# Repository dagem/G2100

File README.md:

# G2100
  a Cherry G80-2100 with modern features

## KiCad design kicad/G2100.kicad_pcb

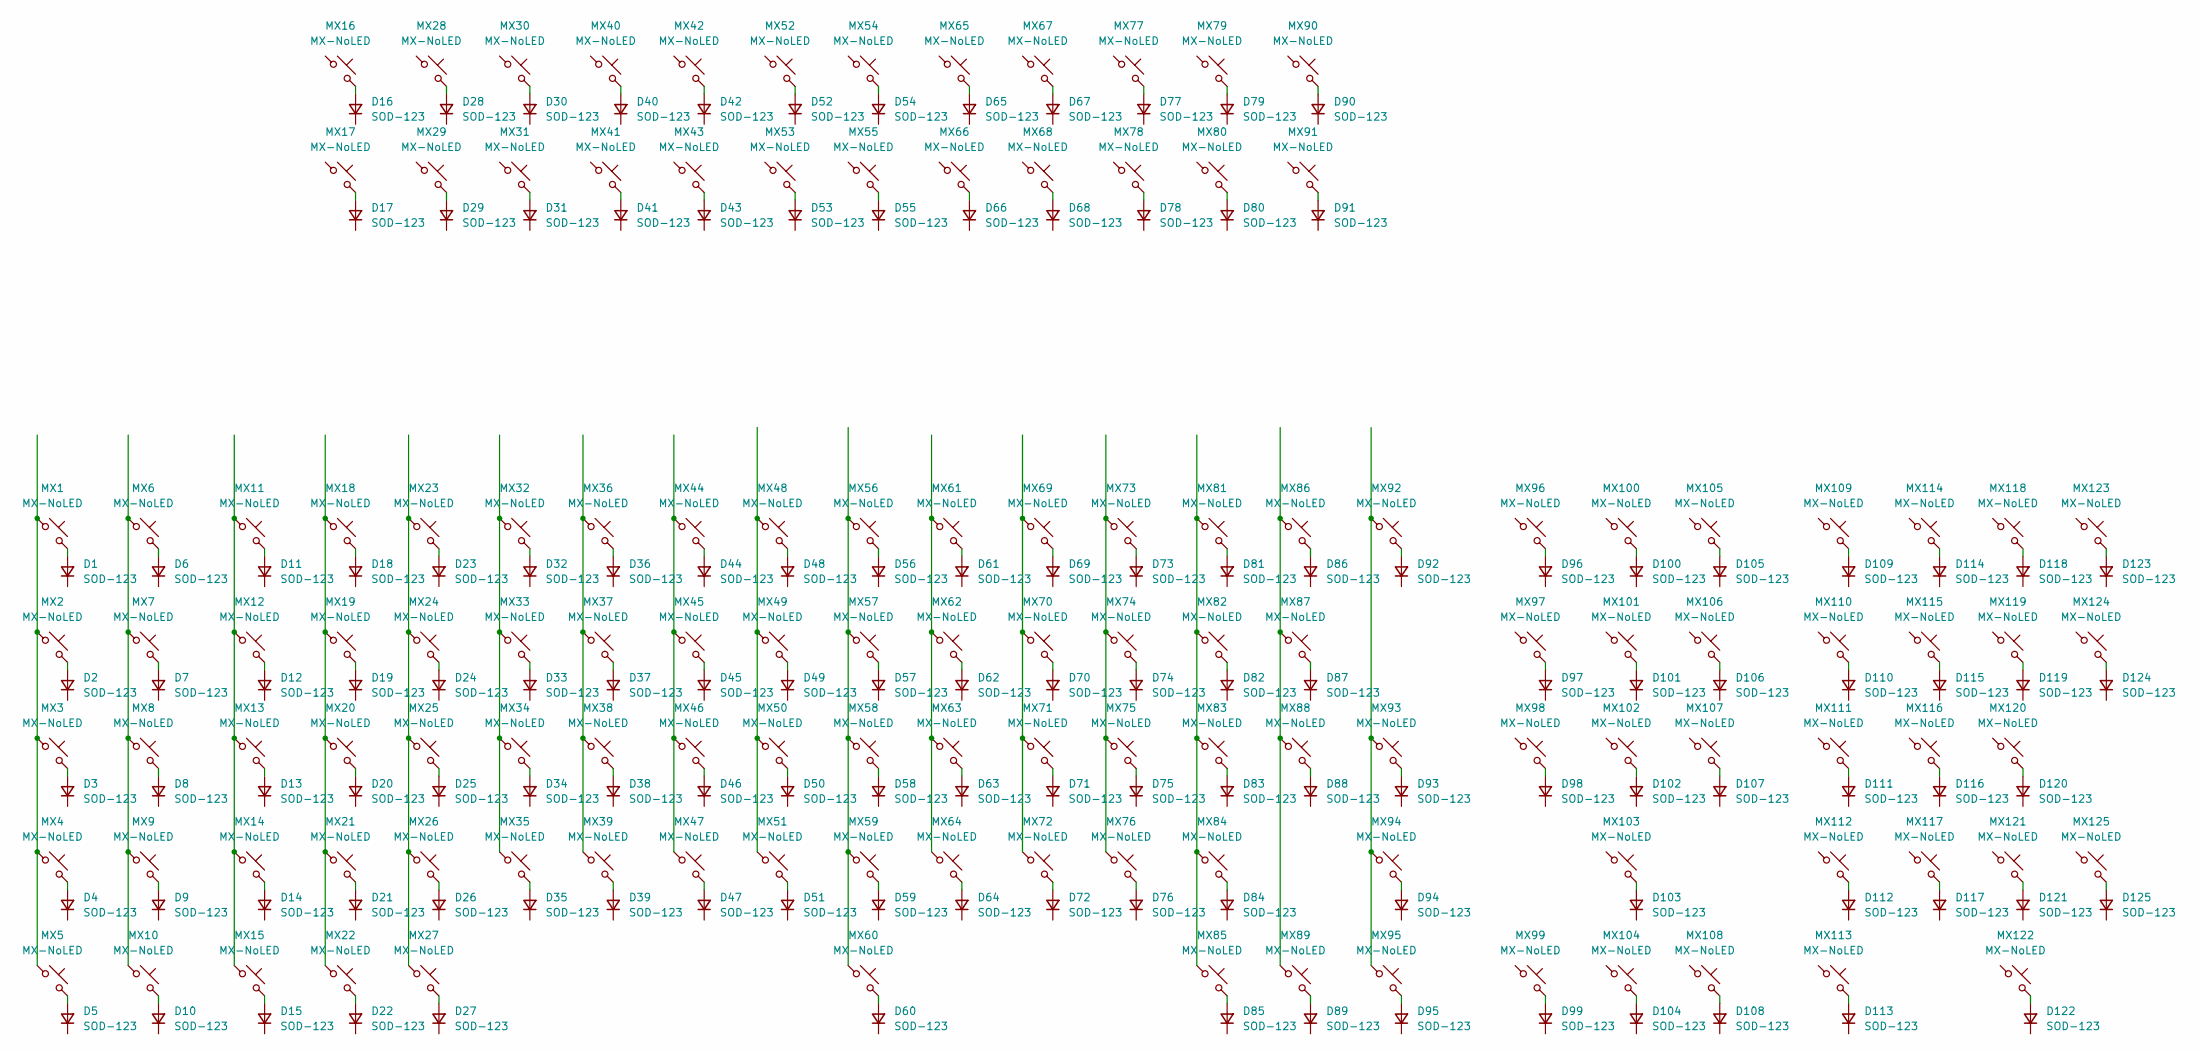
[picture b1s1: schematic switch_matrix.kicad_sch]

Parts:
D1, D2, D3, D4, D5, D6, D7, D8, D9, D10, D11, D12, D13, D14, D15, D16, D17, D18, D19, D20, D21, D22, D23, D24, D25, D26, D27, D28, D29, D30, D31, D32, D33, D34, D35, D36, D37, D38, D39, D40, D41, D42, D43, D44, D45, D46, D47, D48, D49, D50, D51, D52, D53, D54, D55, D56, D57, D58, D59, D60, D61, D62, D63, D64, D65, D66, D67, D68, D69, D70, D71, D72, D73, D74, D75, D76, D77, D78, D79, D80, D81, D82, D83, D84, D85, D86, D87, D88, D89, D90, D91, D92, D93, D94, D95, D96, D97, D98, D99, D100, D101, D102, D103, D104, D105, D106, D107, D108, D109, D110, D111, D112, D113, D114, D115, D116, D117, D118, D119, D120, D121, D122, D123, D124, D125: SOD-123; D_SOD-123
MX1, MX2, MX3, MX4, MX5, MX6, MX7, MX8, MX9, MX10, MX11, MX16, MX17, MX18, MX19, MX20, MX21, MX22, MX23, MX24, MX25, MX26, MX28, MX29, MX30, MX31, MX32, MX33, MX34, MX35, MX36, MX37, MX38, MX39, MX40, MX41, MX42, MX43, MX44, MX45, MX46, MX47, MX48, MX49, MX50, MX51, MX52, MX53, MX54, MX55, MX56, MX57, MX58, MX59, MX61, MX62, MX63, MX64, MX65, MX66, MX67, MX68, MX69, MX70, MX71, MX72, MX73, MX74, MX75, MX76, MX77, MX78, MX79, MX80, MX81, MX82, MX83, MX84, MX86, MX87, MX88, MX89, MX90, MX91, MX96, MX97, MX98, MX99, MX100, MX101, MX102, MX103, MX104, MX105, MX106, MX107, MX108, MX109, MX110, MX111, MX112, MX114, MX115, MX116, MX117, MX118, MX119, MX120, MX121, MX122, MX123: MX-NoLED; MX-Hotswap-1U
MX12, MX15, MX27, MX85, MX95: MX-NoLED; MX-Hotswap-1.5U
MX13: MX-NoLED; MX-Hotswap-1.75U
MX14: MX-NoLED; MX-Hotswap-1.25U
MX60: MX-NoLED; MX-Hotswap-7U
MX92, MX113: MX-NoLED; MX-Hotswap-2U
MX93: MX-NoLED; MX-Hotswap-ISO-Rotated
MX94: MX-NoLED; MX-Hotswap-2.75U
MX124, MX125: MX-NoLED; MX-Hotswap-2U-Vertical

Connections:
unnamed: D1.2 (A_2), MX1.2
unnamed: D2.2 (A_2), MX2.2
unnamed: D3.2 (A_2), MX3.2
unnamed: D4.2 (A_2), MX4.2
unnamed: D5.2 (A_2), MX5.2
unnamed: D6.2 (A_2), MX6.2
unnamed: D7.2 (A_2), MX7.2
unnamed: D8.2 (A_2), MX8.2
unnamed: D9.2 (A_2), MX9.2
unnamed: D10.2 (A_2), MX10.2
unnamed: D11.2 (A_2), MX11.2
unnamed: D12.2 (A_2), MX12.2
unnamed: D13.2 (A_2), MX13.2
unnamed: D14.2 (A_2), MX14.2
unnamed: D15.2 (A_2), MX15.2
unnamed: D16.2 (A_2), MX16.2 (2_2)
unnamed: D17.2 (A_2), MX17.2 (2_2)
unnamed: D18.2 (A_2), MX18.2
unnamed: D19.2 (A_2), MX19.2
unnamed: D20.2 (A_2), MX20.2
unnamed: D21.2 (A_2), MX21.2
unnamed: D22.2 (A_2), MX22.2
unnamed: D23.2 (A_2), MX23.2
unnamed: D24.2 (A_2), MX24.2
unnamed: D25.2 (A_2), MX25.2
unnamed: D26.2 (A_2), MX26.2
unnamed: D27.2 (A_2), MX27.2
unnamed: D28.2 (A_2), MX28.2 (2_2)
unnamed: D29.2 (A_2), MX29.2 (2_2)
unnamed: D30.2 (A_2), MX30.2 (2_2)
unnamed: D31.2 (A_2), MX31.2 (2_2)
unnamed: D32.2 (A_2), MX32.2
unnamed: D33.2 (A_2), MX33.2
unnamed: D34.2 (A_2), MX34.2
unnamed: D35.2 (A_2), MX35.2
unnamed: D36.2 (A_2), MX36.2
unnamed: D37.2 (A_2), MX37.2
unnamed: D38.2 (A_2), MX38.2
unnamed: D39.2 (A_2), MX39.2
unnamed: D40.2 (A_2), MX40.2 (2_2)
unnamed: D41.2 (A_2), MX41.2 (2_2)
unnamed: D42.2 (A_2), MX42.2 (2_2)
unnamed: D43.2 (A_2), MX43.2 (2_2)
unnamed: D44.2 (A_2), MX44.2
unnamed: D45.2 (A_2), MX45.2
unnamed: D46.2 (A_2), MX46.2
unnamed: D47.2 (A_2), MX47.2
unnamed: D48.2 (A_2), MX48.2
unnamed: D49.2 (A_2), MX49.2
unnamed: D50.2 (A_2), MX50.2
unnamed: D51.2 (A_2), MX51.2
unnamed: D52.2 (A_2), MX52.2 (2_2)
unnamed: D53.2 (A_2), MX53.2 (2_2)
unnamed: D54.2 (A_2), MX54.2 (2_2)
unnamed: D55.2 (A_2), MX55.2 (2_2)
unnamed: D56.2 (A_2), MX56.2
unnamed: D57.2 (A_2), MX57.2
unnamed: D58.2 (A_2), MX58.2
unnamed: D59.2 (A_2), MX59.2
unnamed: D60.2 (A_2), MX60.2
unnamed: D61.2 (A_2), MX61.2
unnamed: D62.2 (A_2), MX62.2
unnamed: D63.2 (A_2), MX63.2
unnamed: D64.2 (A_2), MX64.2
unnamed: D65.2 (A_2), MX65.2 (2_2)
unnamed: D66.2 (A_2), MX66.2 (2_2)
unnamed: D67.2 (A_2), MX67.2 (2_2)
unnamed: D68.2 (A_2), MX68.2 (2_2)
unnamed: D69.2 (A_2), MX69.2
unnamed: D70.2 (A_2), MX70.2
unnamed: D71.2 (A_2), MX71.2
unnamed: D72.2 (A_2), MX72.2
unnamed: D73.2 (A_2), MX73.2
unnamed: D74.2 (A_2), MX74.2
unnamed: D75.2 (A_2), MX75.2
unnamed: D76.2 (A_2), MX76.2
unnamed: D77.2 (A_2), MX77.2 (2_2)
unnamed: D78.2 (A_2), MX78.2 (2_2)
unnamed: D79.2 (A_2), MX79.2 (2_2)
unnamed: D80.2 (A_2), MX80.2 (2_2)
unnamed: D81.2 (A_2), MX81.2
unnamed: D82.2 (A_2), MX82.2
unnamed: D83.2 (A_2), MX83.2
unnamed: D84.2 (A_2), MX84.2
unnamed: D85.2 (A_2), MX85.2
unnamed: D86.2 (A_2), MX86.2
unnamed: D87.2 (A_2), MX87.2
unnamed: D88.2 (A_2), MX88.2
unnamed: D89.2 (A_2), MX89.2
unnamed: D90.2 (A_2), MX90.2 (2_2)
unnamed: D91.2 (A_2), MX91.2 (2_2)
unnamed: D92.2 (A_2), MX92.2
unnamed: D93.2 (A_2), MX93.2
unnamed: D94.2 (A_2), MX94.2
unnamed: D95.2 (A_2), MX95.2
unnamed: D96.2 (A_2), MX96.2 (2_2)
unnamed: D97.2 (A_2), MX97.2 (2_2)
unnamed: D98.2 (A_2), MX98.2 (2_2)
unnamed: D99.2 (A_2), MX99.2 (2_2)
unnamed: D100.2 (A_2), MX100.2 (2_2)
unnamed: D101.2 (A_2), MX101.2 (2_2)
unnamed: D102.2 (A_2), MX102.2 (2_2)
unnamed: D103.2 (A_2), MX103.2 (2_2)
unnamed: D104.2 (A_2), MX104.2 (2_2)
unnamed: D105.2 (A_2), MX105.2 (2_2)
unnamed: D106.2 (A_2), MX106.2 (2_2)
unnamed: D107.2 (A_2), MX107.2 (2_2)
unnamed: D108.2 (A_2), MX108.2 (2_2)
unnamed: D109.2 (A_2), MX109.2 (2_2)
unnamed: D110.2 (A_2), MX110.2 (2_2)
unnamed: D111.2 (A_2), MX111.2 (2_2)
unnamed: D112.2 (A_2), MX112.2 (2_2)
unnamed: D113.2 (A_2), MX113.2 (2_2)
unnamed: D114.2 (A_2), MX114.2 (2_2)
unnamed: D115.2 (A_2), MX115.2 (2_2)
unnamed: D116.2 (A_2), MX116.2 (2_2)
unnamed: D117.2 (A_2), MX117.2 (2_2)
unnamed: D118.2 (A_2), MX118.2 (2_2)
unnamed: D119.2 (A_2), MX119.2 (2_2)
unnamed: D120.2 (A_2), MX120.2 (2_2)
unnamed: D121.2 (A_2), MX121.2 (2_2)
unnamed: D122.2 (A_2), MX122.2 (2_2)
unnamed: D123.2 (A_2), MX123.2 (2_2)
unnamed: D124.2 (A_2), MX124.2 (2_2)
unnamed: D125.2 (A_2), MX125.2 (2_2)
unnamed: MX1.1, MX2.1, MX3.1, MX4.1, MX5.1
unnamed: MX6.1, MX7.1, MX8.1, MX9.1, MX10.1
unnamed: MX11.1, MX12.1, MX13.1, MX14.1, MX15.1
unnamed: MX18.1, MX19.1, MX20.1, MX21.1, MX22.1
unnamed: MX23.1, MX24.1, MX25.1, MX26.1, MX27.1
unnamed: MX32.1, MX33.1, MX34.1, MX35.1
unnamed: MX36.1, MX37.1, MX38.1, MX39.1
unnamed: MX44.1, MX45.1, MX46.1, MX47.1
unnamed: MX48.1, MX49.1, MX50.1, MX51.1
unnamed: MX56.1, MX57.1, MX58.1, MX59.1, MX60.1
unnamed: MX61.1, MX62.1, MX63.1, MX64.1
unnamed: MX69.1, MX70.1, MX71.1, MX72.1
unnamed: MX73.1, MX74.1, MX75.1, MX76.1
unnamed: MX81.1, MX82.1, MX83.1, MX84.1, MX85.1
unnamed: MX86.1, MX87.1, MX88.1, MX89.1
unnamed: MX92.1, MX93.1, MX94.1, MX95.1

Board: 2 copper layers, 250 parts (250 on the bottom side), 141 nets, no tracks yet.

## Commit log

2026-04-19 feat: layout switches on pcb
